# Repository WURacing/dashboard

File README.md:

WURacing Dashboard

to use:
virtualenv venv
source /venv/bin/activate
pip install -r requirements.txt
python dashboard.py

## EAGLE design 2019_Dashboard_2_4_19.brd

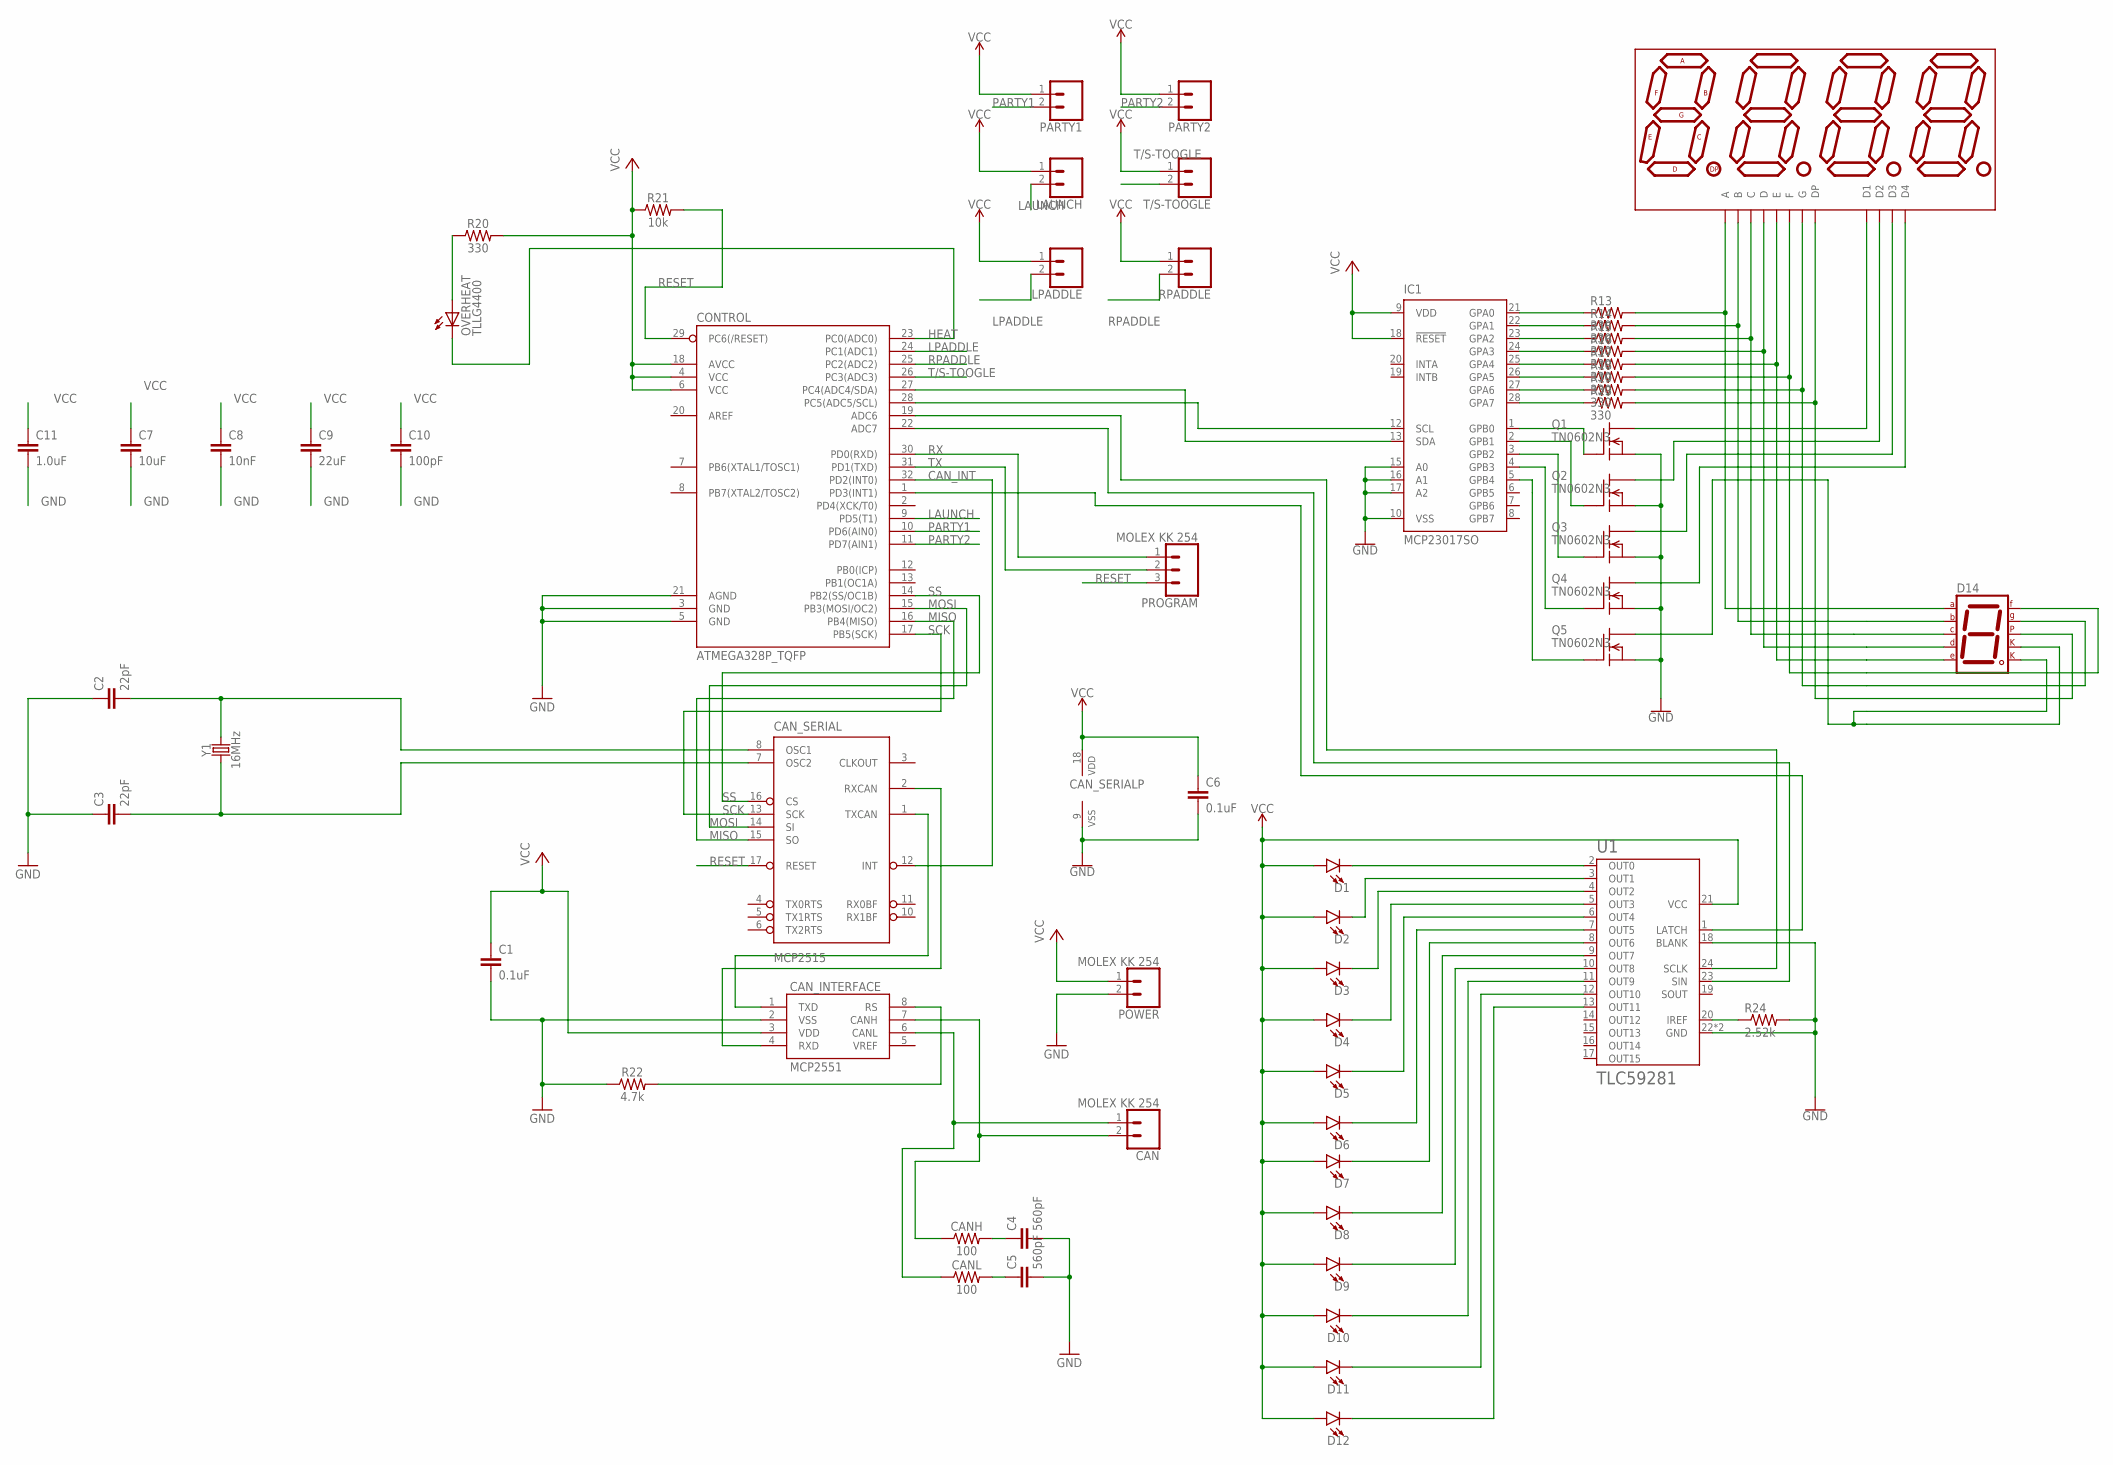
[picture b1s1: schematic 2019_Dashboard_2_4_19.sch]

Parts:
C1: 0.1uF; 0603
C2, C3: 22pF; 0603
C4, C5: 560pF; 0603
C6: 0.1uF; 0402
C7: 10uF; 0805
C8: 10nF; 0603
C9: 22uF; 0805
C10: 100pF; 0603
C11: 1.0uF; 0805
CAN: MOLEX KK 254; 1X02
CANH: 100; 0603
CANL: 100; 0603
CAN_INTERFACE: MCP2551; SO08
CAN_SERIAL: MCP2515; SO18W
CONTROL: ATMEGA328P_TQFP; TQFP32-08
D1, D2, D3, D4, D5, D6, D7, D8, D9, D10, D11, D12: LED5MM; LED_5MM
D14: 7SEG-CK; 7SEG-13
DISP1: ATA8041ARBJ; 7-SEGMENT-4DIGIT-20MM
IC1: MCP23017SO; SO28W
LAUNCH: CONN_02LOCK; 1X02_LOCK
LPADDLE: CONN_02LOCK; 1X02_LOCK
OVERHEAT: TLLG4400; LED3MM
PARTY1, PARTY2: CONN_02LOCK; 1X02_LOCK
POWER: MOLEX KK 254; 1X02
PROGRAM: MOLEX KK 254; 1X03
Q1, Q2, Q3, Q4, Q5: TN0602N3; TO-92
R13, R14, R15, R16, R17, R18, R19, R23: 330; R0603
R20: 330; 0603
R21: 10k; 0603
R22: 4.7k; 0603
R24: 2.52k; R0603
RPADDLE: CONN_02LOCK; 1X02_LOCK
T/S-TOOGLE: CONN_02LOCK; 1X02_LOCK
U1: TLC59281; QFN-24
Y1: 16MHz; HC49US

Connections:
CANH: CAN.2, CANH.1, CAN_INTERFACE.7 (CANH)
CANL: CAN.1, CANL.1, CAN_INTERFACE.6 (CANL)
CAN_INT: CAN_SERIAL.12 (INT), CONTROL.32 (PD2(INT0))
CHI: C4.1, CANH.2
CI_SLOPE: CAN_INTERFACE.8 (RS), R22.2
CLI: C5.1, CANL.2
GND: C1.2, C2.1, C3.1, C4.2, C5.2, C6.2, C7.2, C8.2, C9.2, C10.2, C11.2, CAN_INTERFACE.2 (VSS), CAN_SERIAL.9 (VSS), CONTROL.3 (GND), CONTROL.5 (GND), CONTROL.21 (AGND), IC1.10 (VSS), IC1.15 (A0), IC1.16 (A1), IC1.17 (A2), POWER.2, Q1.1 (S), Q2.1 (S), Q3.1 (S), Q4.1 (S), Q5.1 (S), R22.1, R24.2, U1.18 (BLANK), U1.22 (GND), U1.EP (GND)
HEAT: CONTROL.23 (PC0(ADC0)), OVERHEAT.K (C)
HEAT+: OVERHEAT.A, R20.1
LAUNCH: CONTROL.9 (PD5(T1)), LAUNCH.2
LPADDLE: CONTROL.24 (PC1(ADC1)), LPADDLE.2
MISO: CAN_SERIAL.15 (SO), CONTROL.16 (PB4(MISO))
MOSI: CAN_SERIAL.14 (SI), CONTROL.15 (PB3(MOSI/OC2))
unnamed: CONTROL.28 (PC5(ADC5/SCL)), IC1.12 (SCL)
unnamed: CONTROL.27 (PC4(ADC4/SDA)), IC1.13 (SDA)
unnamed: D14.7 (A), DISP1.11 (A), R13.2
unnamed: D14.6 (B), DISP1.7 (B), R14.2
unnamed: D14.4 (C), DISP1.4 (C), R15.2
unnamed: D14.2 (D), DISP1.2 (D), R16.2
unnamed: D14.1 (E), DISP1.1 (E), R17.2
unnamed: D14.9 (F), DISP1.10 (F), R18.2
unnamed: D14.10 (G), DISP1.5 (G), R19.2
unnamed: D14.5 (DP), DISP1.3 (DP), R23.2
unnamed: DISP1.12 (D1), Q1.3 (D)
unnamed: DISP1.9 (D2), Q2.3 (D)
unnamed: DISP1.8 (D3), Q3.3 (D)
unnamed: DISP1.6 (D4), Q4.3 (D)
unnamed: D14.3 (CK1), D14.8 (CK2), Q5.3 (D)
unnamed: CONTROL.19 (ADC6), U1.24 (SCLK)
unnamed: CONTROL.22 (ADC7), U1.23 (SIN)
unnamed: CONTROL.1 (PD3(INT1)), U1.1 (LATCH)
unnamed: IC1.21 (GPA0), R13.1
unnamed: IC1.22 (GPA1), R14.1
unnamed: IC1.23 (GPA2), R15.1
unnamed: IC1.24 (GPA3), R16.1
unnamed: IC1.25 (GPA4), R17.1
unnamed: IC1.26 (GPA5), R18.1
unnamed: IC1.27 (GPA6), R19.1
unnamed: IC1.28 (GPA7), R23.1
unnamed: IC1.1 (GPB0), Q1.2 (G)
unnamed: IC1.2 (GPB1), Q2.2 (G)
unnamed: IC1.3 (GPB2), Q3.2 (G)
unnamed: IC1.4 (GPB3), Q4.2 (G)
unnamed: IC1.5 (GPB4), Q5.2 (G)
unnamed: D1.K (C), U1.2 (OUT0)
unnamed: D2.K (C), U1.3 (OUT1)
unnamed: D3.K (C), U1.4 (OUT2)
unnamed: D4.K (C), U1.5 (OUT3)
unnamed: CAN_INTERFACE.1 (TXD), CAN_SERIAL.1 (TXCAN)
unnamed: CAN_INTERFACE.4 (RXD), CAN_SERIAL.2 (RXCAN)
unnamed: D5.K (C), U1.6 (OUT4)
unnamed: D6.K (C), U1.7 (OUT5)
unnamed: D7.K (C), U1.8 (OUT6)
unnamed: D8.K (C), U1.9 (OUT7)
unnamed: D9.K (C), U1.10 (OUT8)
unnamed: D10.K (C), U1.11 (OUT9)
unnamed: D11.K (C), U1.12 (OUT10)
unnamed: D12.K (C), U1.13 (OUT11)
unnamed: R24.1, U1.20 (IREF)
OSC1: C2.2, CAN_SERIAL.8 (OSC1), Y1.2
OSC2: C3.2, CAN_SERIAL.7 (OSC2), Y1.1
PARTY1: CONTROL.10 (PD6(AIN0)), PARTY1.2
PARTY2: CONTROL.11 (PD7(AIN1)), PARTY2.2
RESET: CAN_SERIAL.17 (RESET), CONTROL.29 (PC6(/RESET)), PROGRAM.3, R21.2
RPADDLE: CONTROL.25 (PC2(ADC2)), RPADDLE.2
RX: CONTROL.30 (PD0(RXD)), PROGRAM.1
SCK: CAN_SERIAL.13 (SCK), CONTROL.17 (PB5(SCK))
SS: CAN_SERIAL.16 (CS), CONTROL.14 (PB2(SS/OC1B))
T/S-TOOGLE: CONTROL.26 (PC3(ADC3)), T/S-TOOGLE.2
TX: CONTROL.31 (PD1(TXD)), PROGRAM.2
VCC: C1.1, C6.1, C7.1, C8.1, C9.1, C10.1, C11.1, CAN_INTERFACE.3 (VDD), CAN_SERIAL.18 (VDD), CONTROL.4 (VCC), CONTROL.6 (VCC), CONTROL.18 (AVCC), D1.A, D2.A, D3.A, D4.A, D5.A, D6.A, D7.A, D8.A, D9.A, D10.A, D11.A, D12.A, IC1.9 (VDD), IC1.18 (!RESET), LAUNCH.1, LPADDLE.1, PARTY1.1, PARTY2.1, POWER.1, R20.2, R21.1, RPADDLE.1, T/S-TOOGLE.1, U1.21 (VCC)

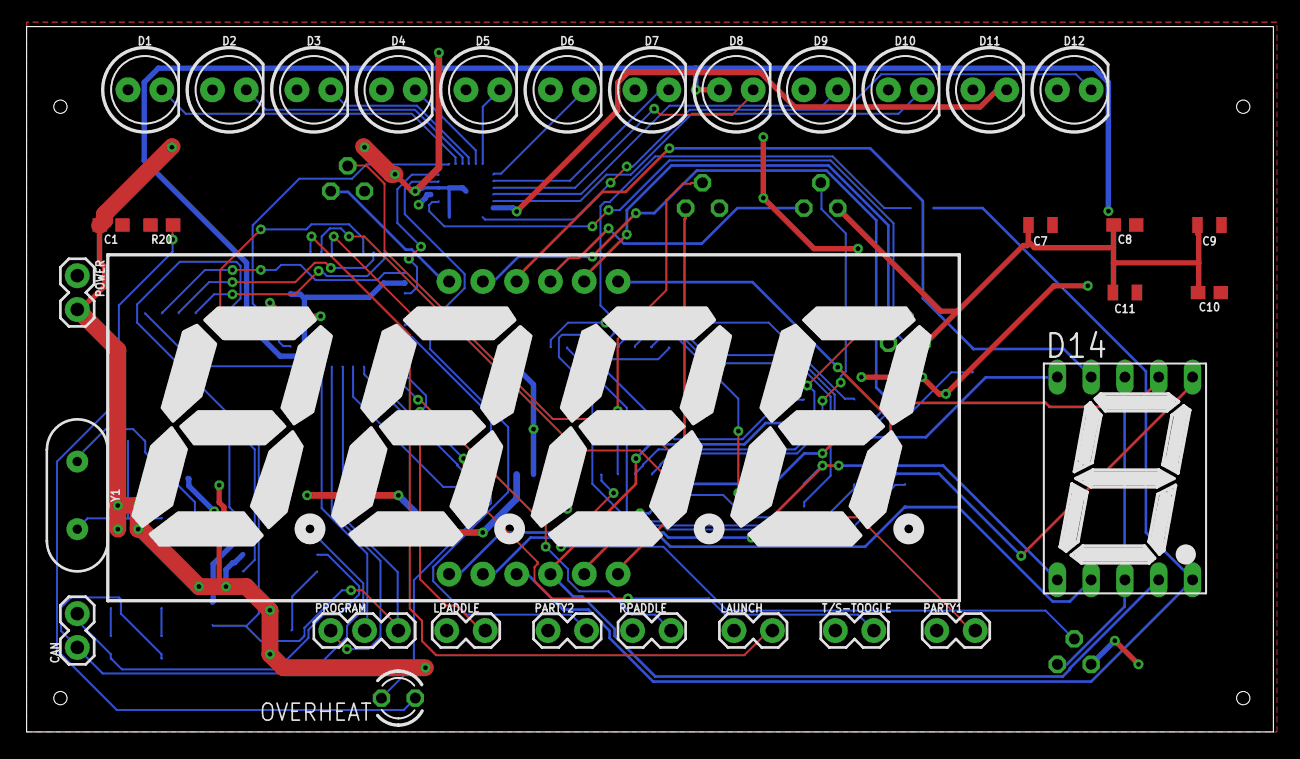
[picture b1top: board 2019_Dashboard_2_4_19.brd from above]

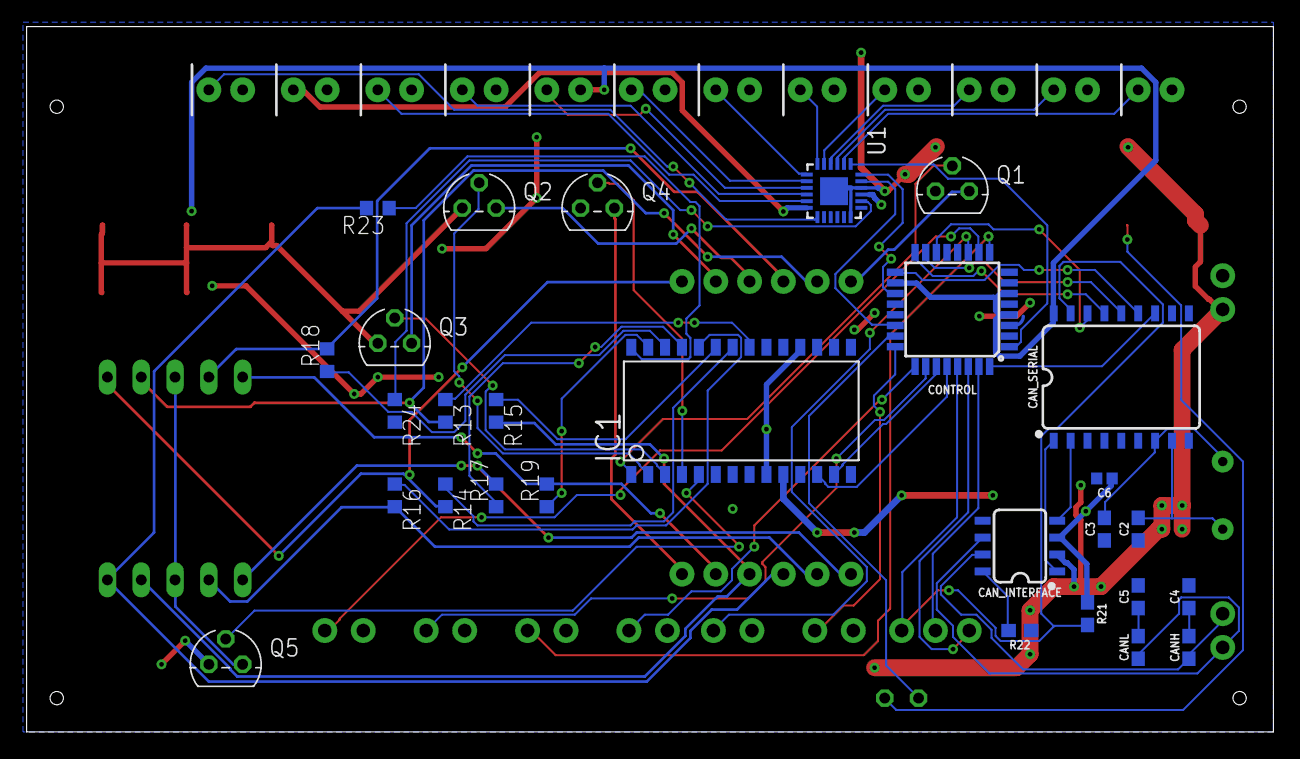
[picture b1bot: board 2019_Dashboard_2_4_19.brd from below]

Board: 2 copper layers, 93.7 x 53.0 mm, 60 parts (28 on the bottom side), 71 nets.

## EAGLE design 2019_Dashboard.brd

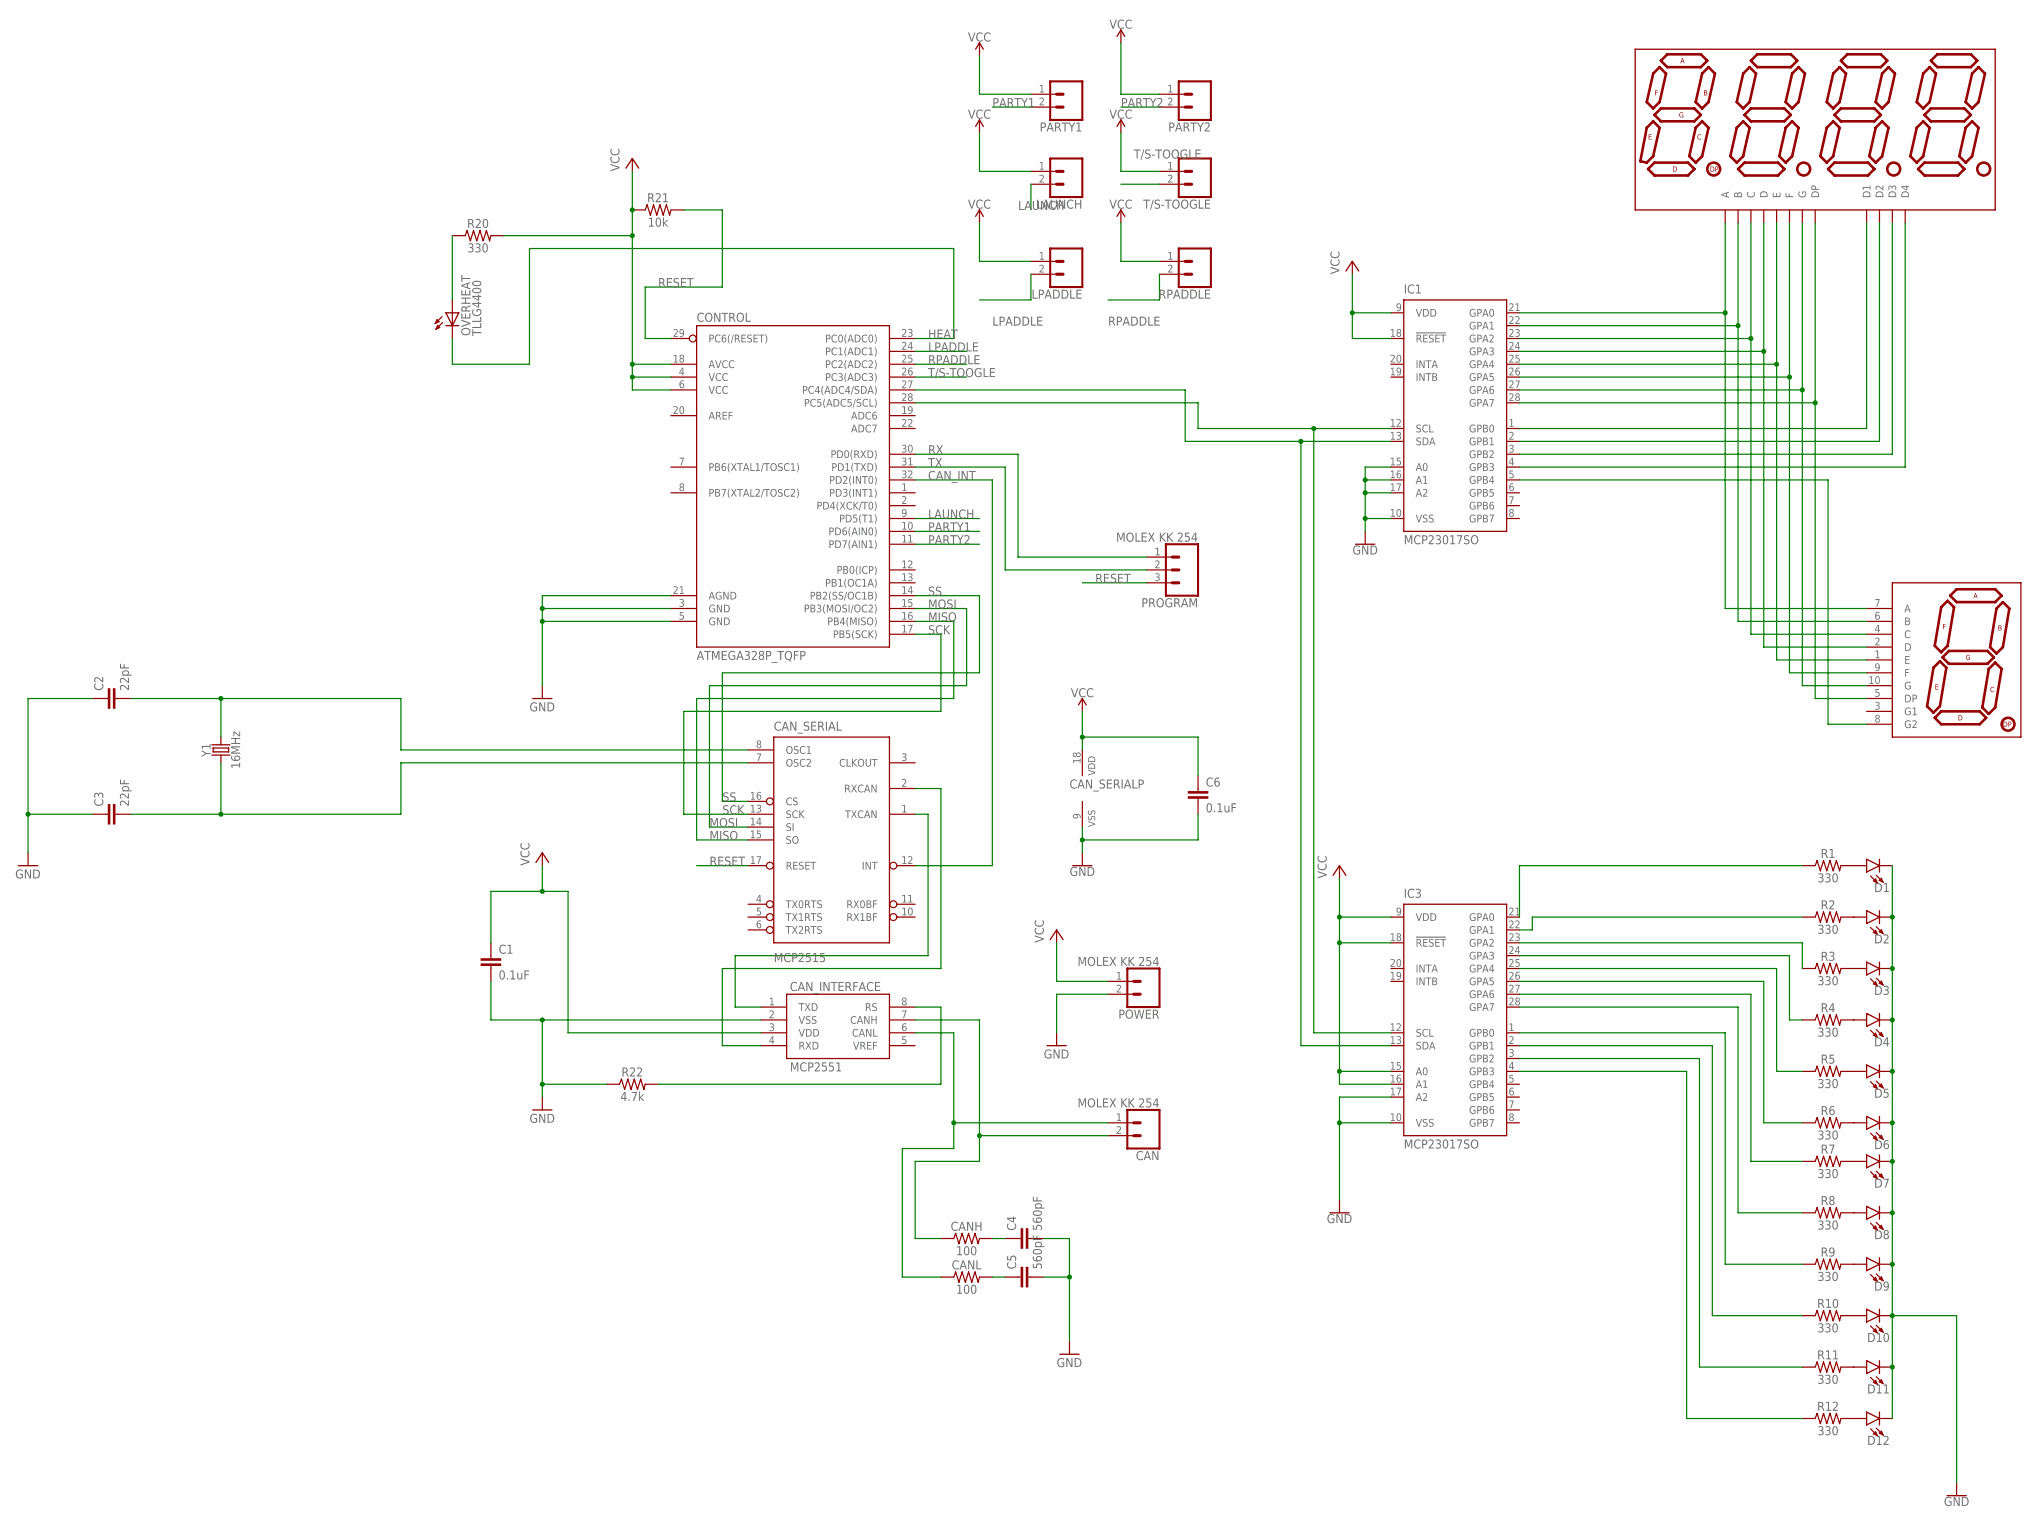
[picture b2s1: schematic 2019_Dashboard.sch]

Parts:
C1: 0.1uF; 0603
C2, C3: 22pF; 0603
C4, C5: 560pF; 0603
C6: 0.1uF; 0402
CAN: MOLEX KK 254; 1X02
CANH: 100; 0603
CANL: 100; 0603
CAN_INTERFACE: MCP2551; SO08
CAN_SERIAL: MCP2515; SO18W
CONTROL: ATMEGA328P_TQFP; TQFP32-08
D1, D2, D3, D4, D5, D6, D7, D8, D9, D10, D11, D12: LED5MM; LED_5MM
DISP1: ATA8041ARBJ; 7-SEGMENT-4DIGIT-20MM
IC1, IC3: MCP23017SO; SO28W
LAUNCH: CONN_02LOCK; 1X02_LOCK
LPADDLE: CONN_02LOCK; 1X02_LOCK
OVERHEAT: TLLG4400; LED3MM
PARTY1, PARTY2: CONN_02LOCK; 1X02_LOCK
POWER: MOLEX KK 254; 1X02
PROGRAM: MOLEX KK 254; 1X03
R1, R2, R3, R4, R5, R6, R7, R8, R9, R10, R11, R12, R20: 330; 0603
R21: 10k; 0603
R22: 4.7k; 0603
RPADDLE: CONN_02LOCK; 1X02_LOCK
T/S-TOOGLE: CONN_02LOCK; 1X02_LOCK
U$1: YSD-1601AR4B-8; 7-SEGMENT-1"PTH
Y1: 16MHz; HC49US

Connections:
CANH: CAN.2, CANH.1, CAN_INTERFACE.7 (CANH)
CANL: CAN.1, CANL.1, CAN_INTERFACE.6 (CANL)
CAN_INT: CAN_SERIAL.12 (INT), CONTROL.32 (PD2(INT0))
CHI: C4.1, CANH.2
CI_SLOPE: CAN_INTERFACE.8 (RS), R22.2
CLI: C5.1, CANL.2
GND: C1.2, C2.1, C3.1, C4.2, C5.2, C6.2, CAN_INTERFACE.2 (VSS), CAN_SERIAL.9 (VSS), CONTROL.3 (GND), CONTROL.5 (GND), CONTROL.21 (AGND), D1.K (C), D2.K (C), D3.K (C), D4.K (C), D5.K (C), D6.K (C), D7.K (C), D8.K (C), D9.K (C), D10.K (C), D11.K (C), D12.K (C), IC1.10 (VSS), IC1.15 (A0), IC1.16 (A1), IC1.17 (A2), IC3.10 (VSS), IC3.17 (A2), POWER.2, R22.1
HEAT: CONTROL.23 (PC0(ADC0)), OVERHEAT.K (C)
HEAT+: OVERHEAT.A, R20.1
LAUNCH: CONTROL.9 (PD5(T1)), LAUNCH.2
LPADDLE: CONTROL.24 (PC1(ADC1)), LPADDLE.2
MISO: CAN_SERIAL.15 (SO), CONTROL.16 (PB4(MISO))
MOSI: CAN_SERIAL.14 (SI), CONTROL.15 (PB3(MOSI/OC2))
unnamed: CONTROL.28 (PC5(ADC5/SCL)), IC1.12 (SCL), IC3.12 (SCL)
unnamed: CONTROL.27 (PC4(ADC4/SDA)), IC1.13 (SDA), IC3.13 (SDA)
unnamed: DISP1.11 (A), IC1.21 (GPA0), U$1.7 (A)
unnamed: DISP1.7 (B), IC1.22 (GPA1), U$1.6 (B)
unnamed: DISP1.4 (C), IC1.23 (GPA2), U$1.4 (C)
unnamed: DISP1.2 (D), IC1.24 (GPA3), U$1.2 (D)
unnamed: DISP1.1 (E), IC1.25 (GPA4), U$1.1 (E)
unnamed: DISP1.10 (F), IC1.26 (GPA5), U$1.9 (F)
unnamed: DISP1.5 (G), IC1.27 (GPA6), U$1.10 (G)
unnamed: DISP1.3 (DP), IC1.28 (GPA7), U$1.5 (DP)
unnamed: DISP1.12 (D1), IC1.1 (GPB0)
unnamed: DISP1.9 (D2), IC1.2 (GPB1)
unnamed: DISP1.8 (D3), IC1.3 (GPB2)
unnamed: DISP1.6 (D4), IC1.4 (GPB3)
unnamed: IC1.5 (GPB4), U$1.8 (G2)
unnamed: D1.A, R1.2
unnamed: D2.A, R2.2
unnamed: D3.A, R3.2
unnamed: D4.A, R4.2
unnamed: D5.A, R5.2
unnamed: D6.A, R6.2
unnamed: D7.A, R7.2
unnamed: D8.A, R8.2
unnamed: D9.A, R9.2
unnamed: D10.A, R10.2
unnamed: D11.A, R11.2
unnamed: D12.A, R12.2
unnamed: IC3.21 (GPA0), R1.1
unnamed: IC3.22 (GPA1), R2.1
unnamed: IC3.23 (GPA2), R3.1
unnamed: IC3.24 (GPA3), R4.1
unnamed: IC3.25 (GPA4), R5.1
unnamed: IC3.26 (GPA5), R6.1
unnamed: IC3.27 (GPA6), R7.1
unnamed: IC3.28 (GPA7), R8.1
unnamed: IC3.1 (GPB0), R9.1
unnamed: IC3.2 (GPB1), R10.1
unnamed: IC3.3 (GPB2), R11.1
unnamed: IC3.4 (GPB3), R12.1
unnamed: CAN_INTERFACE.1 (TXD), CAN_SERIAL.1 (TXCAN)
unnamed: CAN_INTERFACE.4 (RXD), CAN_SERIAL.2 (RXCAN)
OSC1: C2.2, CAN_SERIAL.8 (OSC1), Y1.2
OSC2: C3.2, CAN_SERIAL.7 (OSC2), Y1.1
PARTY1: CONTROL.10 (PD6(AIN0)), PARTY1.2
PARTY2: CONTROL.11 (PD7(AIN1)), PARTY2.2
RESET: CAN_SERIAL.17 (RESET), CONTROL.29 (PC6(/RESET)), PROGRAM.3, R21.2
RPADDLE: CONTROL.25 (PC2(ADC2)), RPADDLE.2
RX: CONTROL.30 (PD0(RXD)), PROGRAM.1
SCK: CAN_SERIAL.13 (SCK), CONTROL.17 (PB5(SCK))
SS: CAN_SERIAL.16 (CS), CONTROL.14 (PB2(SS/OC1B))
T/S-TOOGLE: CONTROL.26 (PC3(ADC3)), T/S-TOOGLE.2
TX: CONTROL.31 (PD1(TXD)), PROGRAM.2
VCC: C1.1, C6.1, CAN_INTERFACE.3 (VDD), CAN_SERIAL.18 (VDD), CONTROL.4 (VCC), CONTROL.6 (VCC), CONTROL.18 (AVCC), IC1.9 (VDD), IC1.18 (!RESET), IC3.9 (VDD), IC3.15 (A0), IC3.16 (A1), IC3.18 (!RESET), LAUNCH.1, LPADDLE.1, PARTY1.1, PARTY2.1, POWER.1, R20.2, R21.1, RPADDLE.1, T/S-TOOGLE.1

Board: 2 copper layers, 53 parts (8 on the bottom side), 66 nets, no tracks yet.

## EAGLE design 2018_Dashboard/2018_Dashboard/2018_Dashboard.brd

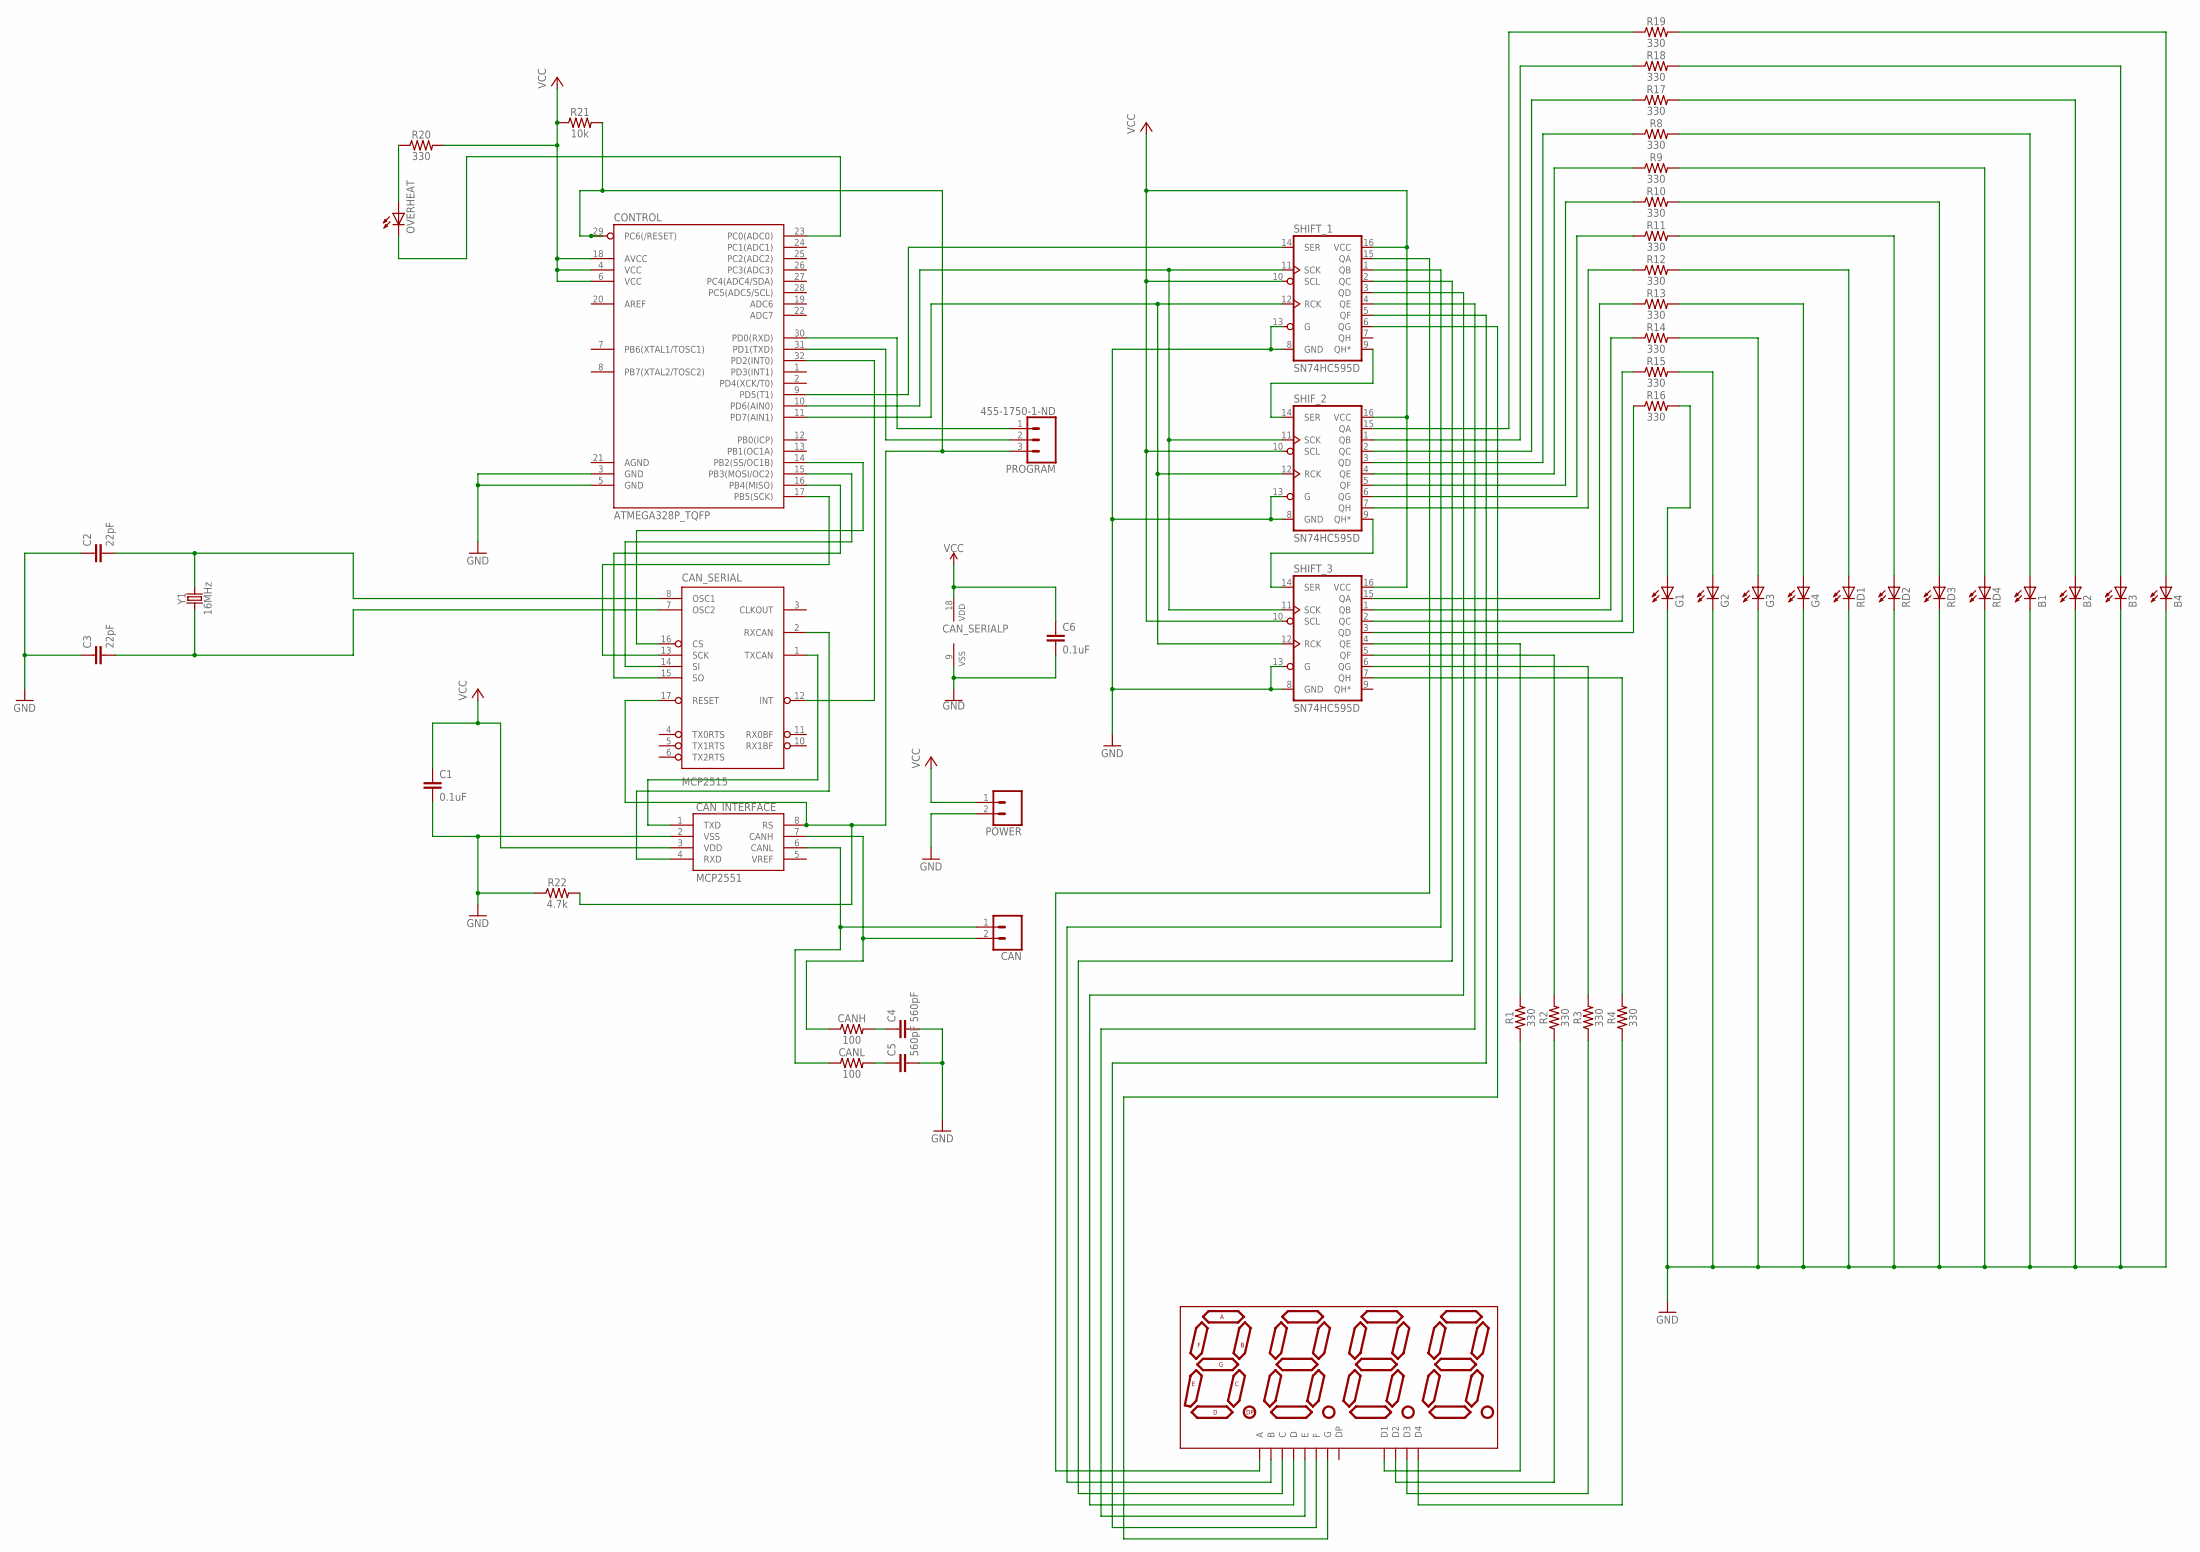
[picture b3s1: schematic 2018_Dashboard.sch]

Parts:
B1, B2, B3, B4: TLLG4400; LED3MM
C1: 0.1uF; 0603
C2, C3: 22pF; 0603
C4, C5: 560pF; 0603
C6: 0.1uF; 0402
CAN: CONN_02; 1X02
CANH: 100; 0603
CANL: 100; 0603
CAN_INTERFACE: MCP2551; SO08
CAN_SERIAL: MCP2515; SO18W
CONTROL: ATMEGA328P_TQFP; TQFP32-08
G1, G2, G3, G4: TLLG4400; LED3MM
OVERHEAT: TLLG4400; LED3MM
POWER: CONN_02; 1X02
PROGRAM: 455-1750-1-ND; 1X03
R1, R2, R3, R4, R8, R9, R10, R11, R12, R13, R14, R15, R16, R17, R18, R19, R20: 330; 0603
R21: 10k; 0603
R22: 4.7k; 0603
RD1, RD2, RD3, RD4: TLLG4400; LED3MM
SEVEN_SEGMENT: ATA8041AB; 7-SEGMENT-4DIGIT-20MM
SHIFT_1, SHIFT_3: SN74HC595D; SO16
SHIF_2: SN74HC595D; SO16
Y1: 16MHz; HC49US

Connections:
CANH: CAN.2, CANH.1, CAN_INTERFACE.7 (CANH)
CANL: CAN.1, CANL.1, CAN_INTERFACE.6 (CANL)
GND: B1.K (C), B2.K (C), B3.K (C), B4.K (C), C1.2, C2.1, C3.1, C4.2, C5.2, C6.2, CAN_INTERFACE.2 (VSS), CAN_SERIAL.9 (VSS), CONTROL.3 (GND), CONTROL.5 (GND), G1.K (C), G2.K (C), G3.K (C), G4.K (C), POWER.2, R22.1, RD1.K (C), RD2.K (C), RD3.K (C), RD4.K (C), SHIFT_1.8 (GND), SHIFT_1.13 (G), SHIFT_3.8 (GND), SHIFT_3.13 (G), SHIF_2.8 (GND), SHIF_2.13 (G)
MISO: CAN_SERIAL.15 (SO), CONTROL.16 (PB4(MISO))
unnamed: SHIFT_1.9 (QH*), SHIF_2.14 (SER)
unnamed: R1.2, SHIFT_3.4 (QE)
unnamed: R2.2, SHIFT_3.5 (QF)
unnamed: R3.2, SHIFT_3.6 (QG)
unnamed: R4.2, SHIFT_3.7 (QH)
unnamed: SHIFT_3.14 (SER), SHIF_2.9 (QH*)
unnamed: SEVEN_SEGMENT.11 (A), SHIFT_1.15 (QA)
unnamed: SEVEN_SEGMENT.7 (B), SHIFT_1.1 (QB)
unnamed: SEVEN_SEGMENT.4 (C), SHIFT_1.2 (QC)
unnamed: SEVEN_SEGMENT.2 (D), SHIFT_1.3 (QD)
unnamed: SEVEN_SEGMENT.1 (E), SHIFT_1.4 (QE)
unnamed: SEVEN_SEGMENT.10 (F), SHIFT_1.5 (QF)
unnamed: SEVEN_SEGMENT.5 (G), SHIFT_1.6 (QG)
unnamed: B2.A, R17.2
unnamed: B3.A, R18.2
unnamed: CONTROL.9 (PD5(T1)), SHIFT_1.14 (SER)
unnamed: CONTROL.10 (PD6(AIN0)), SHIFT_1.11 (SCK), SHIFT_3.11 (SCK), SHIF_2.11 (SCK)
unnamed: CONTROL.11 (PD7(AIN1)), SHIFT_1.12 (RCK), SHIFT_3.12 (RCK), SHIF_2.12 (RCK)
unnamed: B4.A, R19.2
unnamed: R1.1, SEVEN_SEGMENT.12 (D1)
unnamed: R19.1, SHIF_2.15 (QA)
unnamed: R18.1, SHIF_2.1 (QB)
unnamed: R17.1, SHIF_2.2 (QC)
unnamed: R8.1, SHIF_2.3 (QD)
unnamed: G1.A, R16.2
unnamed: G2.A, R15.2
unnamed: G3.A, R14.2
unnamed: G4.A, R13.2
unnamed: R12.2, RD1.A
unnamed: R11.2, RD2.A
unnamed: R10.2, RD3.A
unnamed: R9.2, RD4.A
unnamed: B1.A, R8.2
unnamed: R9.1, SHIF_2.4 (QE)
unnamed: R10.1, SHIF_2.5 (QF)
unnamed: R11.1, SHIF_2.6 (QG)
unnamed: R12.1, SHIF_2.7 (QH)
unnamed: R13.1, SHIFT_3.15 (QA)
unnamed: R14.1, SHIFT_3.1 (QB)
unnamed: R15.1, SHIFT_3.2 (QC)
unnamed: R16.1, SHIFT_3.3 (QD)
unnamed: R2.1, SEVEN_SEGMENT.9 (D2)
unnamed: R3.1, SEVEN_SEGMENT.8 (D3)
unnamed: R4.1, SEVEN_SEGMENT.6 (D4)
unnamed: OVERHEAT.A, R20.1
unnamed: CONTROL.23 (PC0(ADC0)), OVERHEAT.K (C)
unnamed: CAN_SERIAL.16 (CS), CONTROL.14 (PB2(SS/OC1B))
unnamed: CAN_SERIAL.12 (INT), CONTROL.32 (PD2(INT0))
unnamed: CAN_INTERFACE.1 (TXD), CAN_SERIAL.1 (TXCAN)
unnamed: CAN_INTERFACE.4 (RXD), CAN_SERIAL.2 (RXCAN)
unnamed: C3.2, CAN_SERIAL.7 (OSC2), Y1.1
unnamed: C4.1, CANH.2
unnamed: C2.2, CAN_SERIAL.8 (OSC1), Y1.2
unnamed: C5.1, CANL.2
RX: CONTROL.30 (PD0(RXD)), PROGRAM.1
S$2: CAN_SERIAL.14 (SI), CONTROL.15 (PB3(MOSI/OC2))
SCK: CAN_SERIAL.13 (SCK), CONTROL.17 (PB5(SCK))
TX: CONTROL.31 (PD1(TXD)), PROGRAM.2
VCC: C1.1, C6.1, CAN_INTERFACE.3 (VDD), CAN_SERIAL.18 (VDD), CONTROL.4 (VCC), CONTROL.6 (VCC), CONTROL.18 (AVCC), POWER.1, R20.2, R21.1, SHIFT_1.10 (SCL), SHIFT_1.16 (VCC), SHIFT_3.10 (SCL), SHIFT_3.16 (VCC), SHIF_2.10 (SCL), SHIF_2.16 (VCC)

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
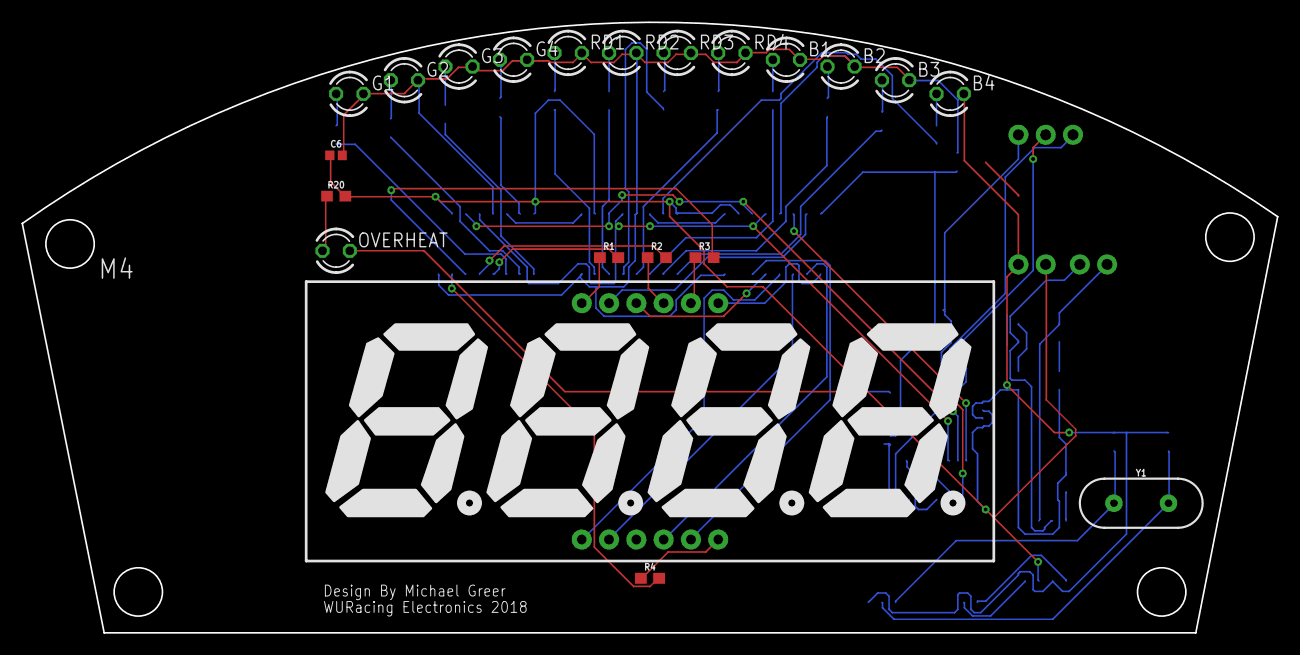
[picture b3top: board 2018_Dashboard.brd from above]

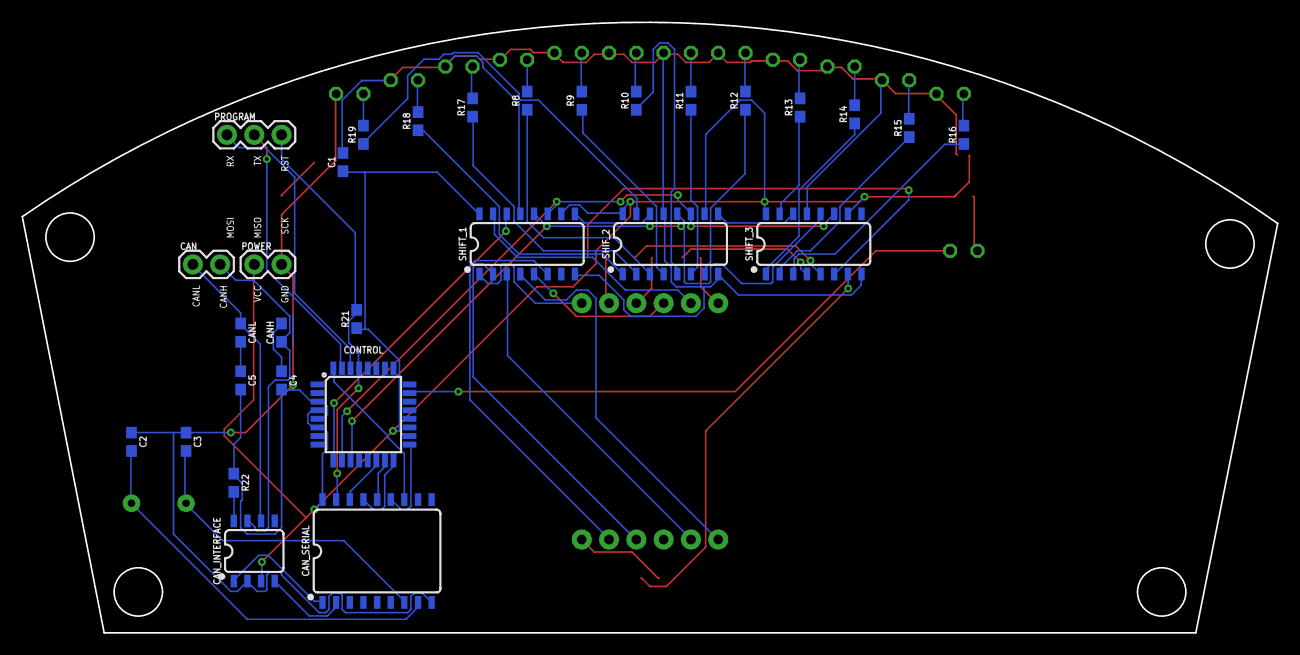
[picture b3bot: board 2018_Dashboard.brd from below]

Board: 2 copper layers, 116.8 x 56.8 mm, 51 parts (30 on the bottom side), 65 nets.

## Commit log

2016-09-23 added dashboard.py to the repo. TODO create python VENV
2016-09-23 created basic dashboard framework
2016-09-24 Added code to generate tick marks
2016-09-24 Added redline function to code
2016-09-25 Added pointer and test animation
2016-09-25 added readme and requirements for virtualenv
2016-09-25 Added number functionality to dashboard.py
2016-09-25 improved scalability
2016-10-01 Added fullscreen functionality
2016-10-01 Added .gitignore
2016-11-12 Added extra fonts and made numerical counters work
2016-12-03 Stopped messing around with fonts. All working fonts are now monaco for readability.
2017-01-21 Added serial communication functionality
2017-01-28 Finished serial data input code
2017-01-28 recent pull
2017-01-28 looks prettier
2017-01-28 rpm added to dial
2017-02-11 added rpmColor
2017-02-11 Added test.png to make Logo Sprite
2017-02-11 added logo sprite (BUGGED)
2017-02-25 Committing gitignore
2017-02-25 Trying again
2017-02-25 Added serial functionality
2017-02-25 removed venv tracking
2017-02-25 Removed git tracking of venv
2017-02-25 Got it to work
2017-02-25 commented out logo stuff
2017-02-26 Slightly changed location of text and added rpm smoothing
2017-02-26 Added load image (racing logo)
2017-03-04 adding draft image
2017-03-04 added newDashboard.py as per New Dashboard Draft.JPG
2017-03-04 newDashboard.py Version 2
2017-03-08 messed around with rpmtext location
2017-03-08 Didn't actually change anything, looks great Matt
2017-03-31 changed display appearance
2017-04-08 made newDashboard.py more to specs
2017-04-11 cleaned up newDashboard.py and added comments
2017-04-23 made things work
2017-04-29 Made some changes
2017-04-29 Added multiple warning and low battery shutoff
2017-04-29 Stuff works now
2017-04-29 Final-ish version
2017-04-30 Got rid of mouse cursor
2017-05-01 Added a statement to block junk battery data, and lowered the battery threshold to 11.5
2017-05-01 temporarily removed low battery shutoff functionality - not working correctly
2017-05-01 Added note on why low battery shutoff was commented out
2017-05-06 Made temperature a little more obvious
2017-05-06 Changed back from testing mode
2017-11-12 dash
2017-11-12 global_val added
2017-11-18 database added
2017-12-09 Moved all 2017 stuff to folder
2018-01-27 Added 2018 Dashboard Directory
2018-02-03 Added board files
2018-02-03 Changed resistors from before seven segment to after seven segment, reduced number of resistors
2018-02-03 Added silkscreen stuff
2018-02-03 Added mounting holes
2018-02-22 fixed power net for can communication
2018-03-25 Post order changes for 2019 car: Made board more narrow Added breakout headers for buring bootloader git commit -m
2018-05-08 Removed Bootloader pins from layout
2018-05-13 Fix "board and schematic are not consistent"
    Also wired up the decimal point because why not
2018-09-24 Backlink to CADLAB.io has been added.
2018-09-29 Add files via upload
    Starting point for the 2019 dashboard using I2C instead of SIPO shift registers.
2018-11-15 Add files via upload
    2019 dashboard schematic as of 11/14, PCB still needs to be done but awaiting design changes,
2018-11-26 11/26/18 I2C Dashboard
2018-11-29 Yeet a few pins
2019-01-15 Add files via upload
    first run at putting down traces, width needs to be adjusted on them and it needs power and ground planes. layout looks okay though.
2019-01-26 Add files via upload
    changed LEDs to Through-hole
2019-01-28 Add files via upload
    replaced one io expander with led driver. Added transistors to common cathodes. Board needs to be arranged and routed still.
2019-01-29 Add files via upload
    redesigned board, please dear god be done
2019-02-02 Add files via upload
    Finished?
2019-02-05 Added correct footprint for gear position display
    Committing before I actually wire it up
2019-02-05 Wired gear position, still needs traces
2019-02-06 Add files via upload
    Dear lord Jesus please let it be done
2019-02-09 Dashboard with Pico-Lock 1.50mm connectors & AVR header & pullup resistors
    https://www.molex.com/molex/products/family?key=picolock&channel=products&chanName=family&pageTitle=Introduction&parentKey=wtb_signal_connectors
2019-03-25 Remove old revisions
2019-03-25 Feel like these should be here
2019-03-25 Updated dashboard schematic, fix post-order bugs
    Board not updated yet

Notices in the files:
parts and their libraries:
SparkFun-Capacitors: Licensing: Creative Commons ShareAlike 4.0 International - https://creativecommons.org/licenses/by-sa/4.0
volks73-Molex: Creative Commons Attribution-ShareAlike 3.0 Unported (CC BY-SA 3.0), http://creativecommons.org/licenses/by-sa/3.0/.
